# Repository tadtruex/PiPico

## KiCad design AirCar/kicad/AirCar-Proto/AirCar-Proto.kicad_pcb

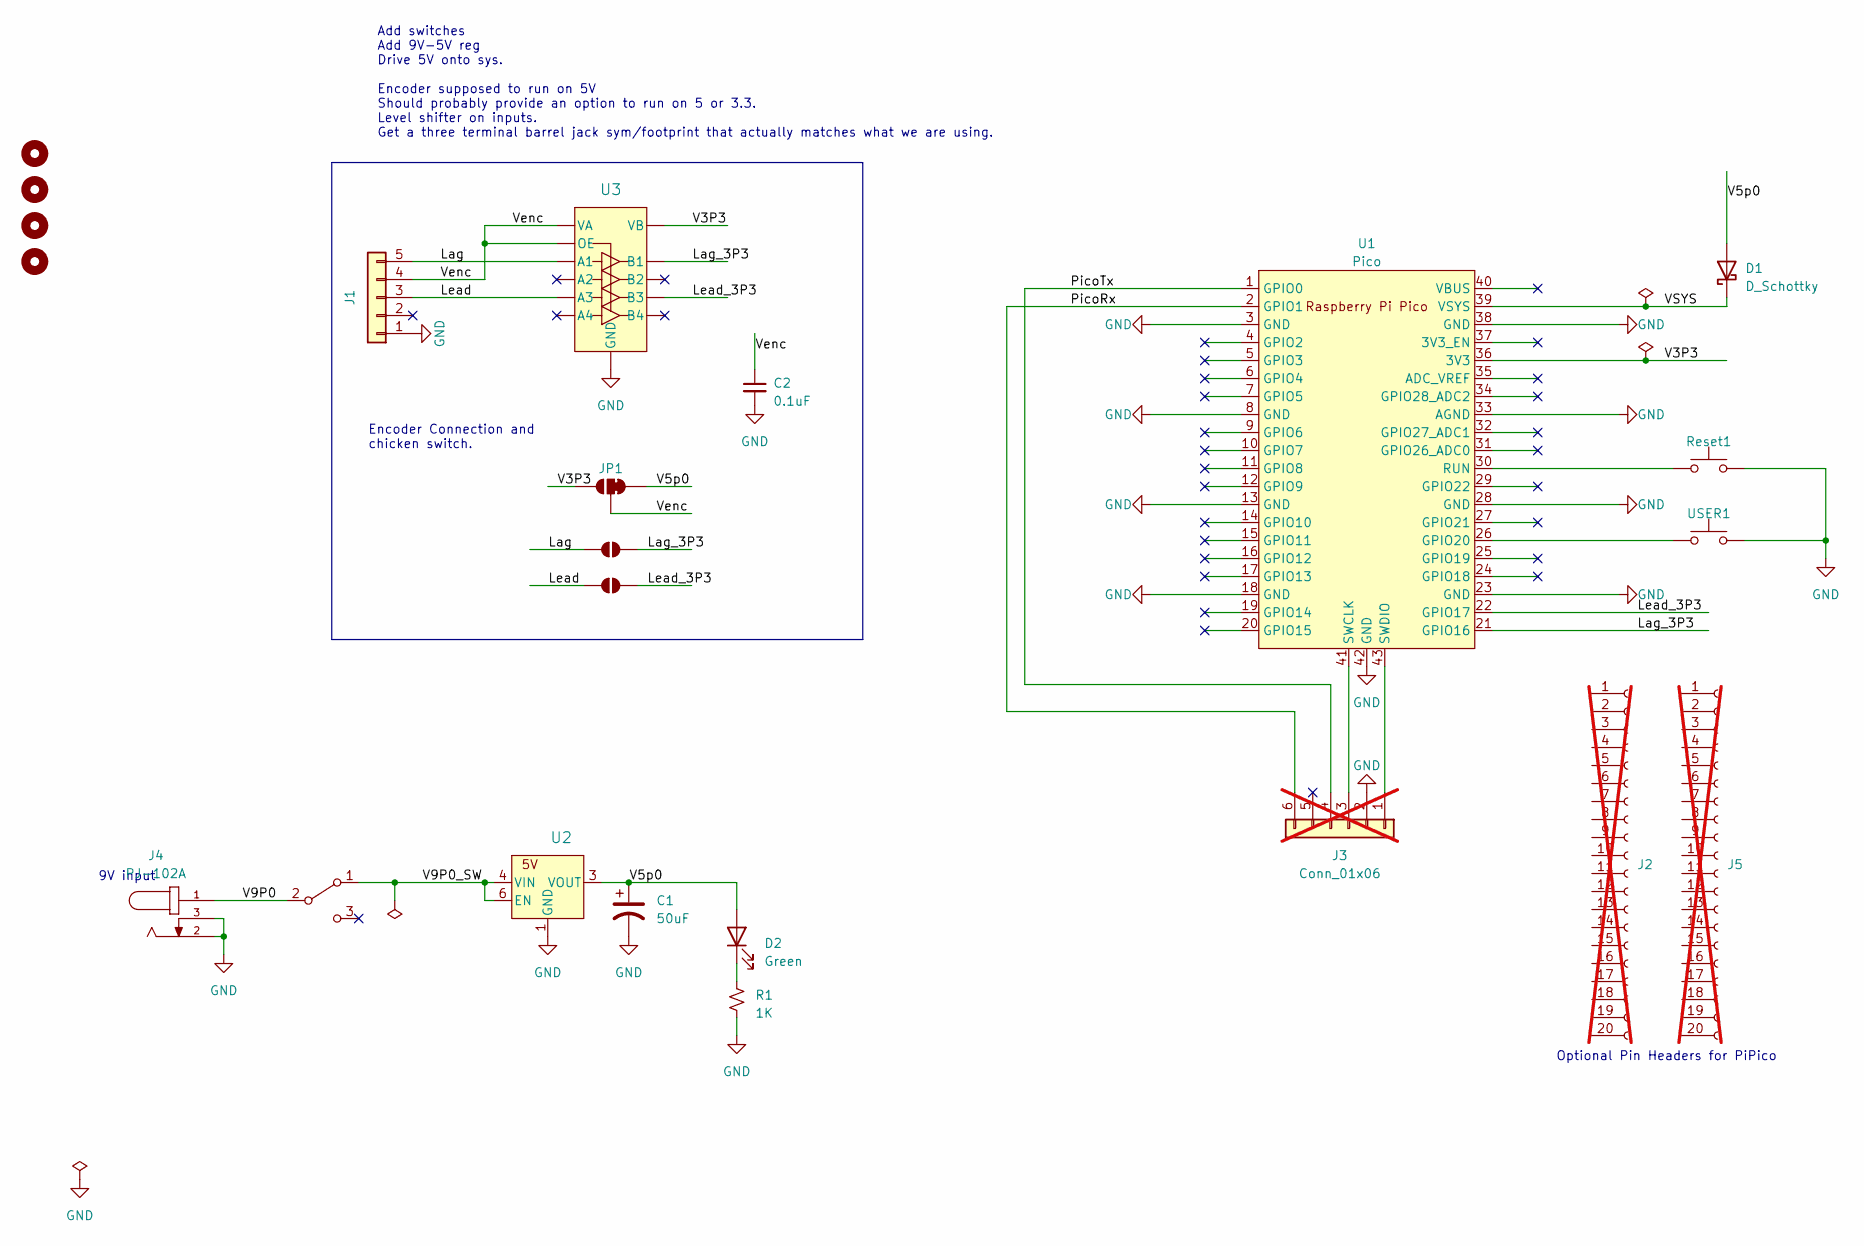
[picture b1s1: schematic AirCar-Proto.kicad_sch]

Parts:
C1: 50uF; CP_Radial_D8.0mm_P2.50mm
C2: 0.1uF; C_0603_1608Metric
D1: D_Schottky; D_SOD-123F; Digikey CRS01QCT-ND
D2: Green; LED_D5.0mm
H1, H2, H3, H4: MountingHole; MountingHole_3.2mm_M3
J1: Conn_01x05; PinHeader_1x05_P2.54mm_Horizontal; Digikey WM4903-ND
J2, J5: Conn_01x20_Socket; PinHeader_1x20_P2.54mm_Vertical; DigiKey 1212-1105-ND; not fitted
J3: Conn_01x06; PinHeader_1x06_P2.54mm_Horizontal; not fitted
J4: PJ-102A; BarrelJack_CUI_PJ-102AH_Horizontal; PART_REV 1.03
JP1: SolderJumper_3_Bridged12; SolderJumper-3_P1.3mm_Bridged12_RoundedPad1.0x1.5mm
JP2, JP3: SolderJumper_2_Open; SolderJumper-2_P1.3mm_Open_RoundedPad1.0x1.5mm
R1: 1K; R_0603_1608Metric
Reset1: SmallPushbutton; SW4_1825910-B_TEC; Digikey 450-1650-ND
SW2: SW_SPDT; CS12ANW03_NKK; Digikey 360-2131-ND
U1: Pico; RPi_Pico_SMD_TH; Digikey 2648-SC0915TR-ND
U2: LDL212PU50R; DFN-6-1EP_3x3mm_P0.95mm_EP1.7x2.6mm; Digikey 497-16897-2-ND
U3: TXU0104BQAR; U_TXU0104_TEX; Digikey 296-TXU0104BQARTR-ND
USER1: SmallPushbutton; SW4_1825910-B_TEC; Digikey 450-1650-ND

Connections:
/Lag: J1.5, JP2.1 (A), U3.2 (A1)
/Lag_3P3: JP2.2 (B), U1.21 (GPIO16), U3.13 (B1)
/Lead: J1.3, JP3.1 (A), U3.4 (A3)
/Lead_3P3: JP3.2 (B), U1.22 (GPIO17), U3.11 (B3)
/PicoRx: J3.6, U1.2 (GPIO1)
/PicoTx: J3.4, U1.1 (GPIO0)
/V3P3: JP1.3 (B), U1.36 (3V3), U3.14 (VB)
/V5p0: C1.1, D1.2 (A), D2.2 (A), JP1.1 (A), U2.2 (ADJ/sense), U2.3 (VOUT)
/V9P0: J4.1, SW2.2 (B)
/V9P0_SW: SW2.1 (A), U2.4 (VIN), U2.6 (EN)
/VSYS: D1.1 (K), U1.39 (VSYS)
/Venc: C2.1, J1.4, JP1.2 (C), U3.1 (VA), U3.8 (OE)
GND: C1.2, C2.2, J1.1, J3.2, J4.2, J4.3, R1.2, Reset1.3, Reset1.4, U1.3 (GND), U1.8 (GND), U1.13 (GND), U1.18 (GND), U1.23 (GND), U1.28 (GND), U1.33 (AGND), U1.38 (GND), U1.42 (GND), U2.1 (GND), U2.7 (GND), U3.7 (GND), U3.15 (GND), USER1.3, USER1.4
unnamed: D2.1 (K), R1.1
unnamed: J3.1, U1.43 (SWDIO)
unnamed: J3.3, U1.41 (SWCLK)
unnamed: U1.26 (GPIO20), USER1.1, USER1.2
unnamed: Reset1.1, Reset1.2, U1.30 (RUN)

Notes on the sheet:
Add switches Add 9V-5V reg Drive 5V onto sys. Encoder supposed to run on 5V Should probably provide an option to run on 5 or 3.3. Level shifter on inputs. Get a three terminal barrel jack sym/footprint that actually matches what we are using.
Optional Pin Headers for PiPico
9V input
Encoder Connection and chicken switch.

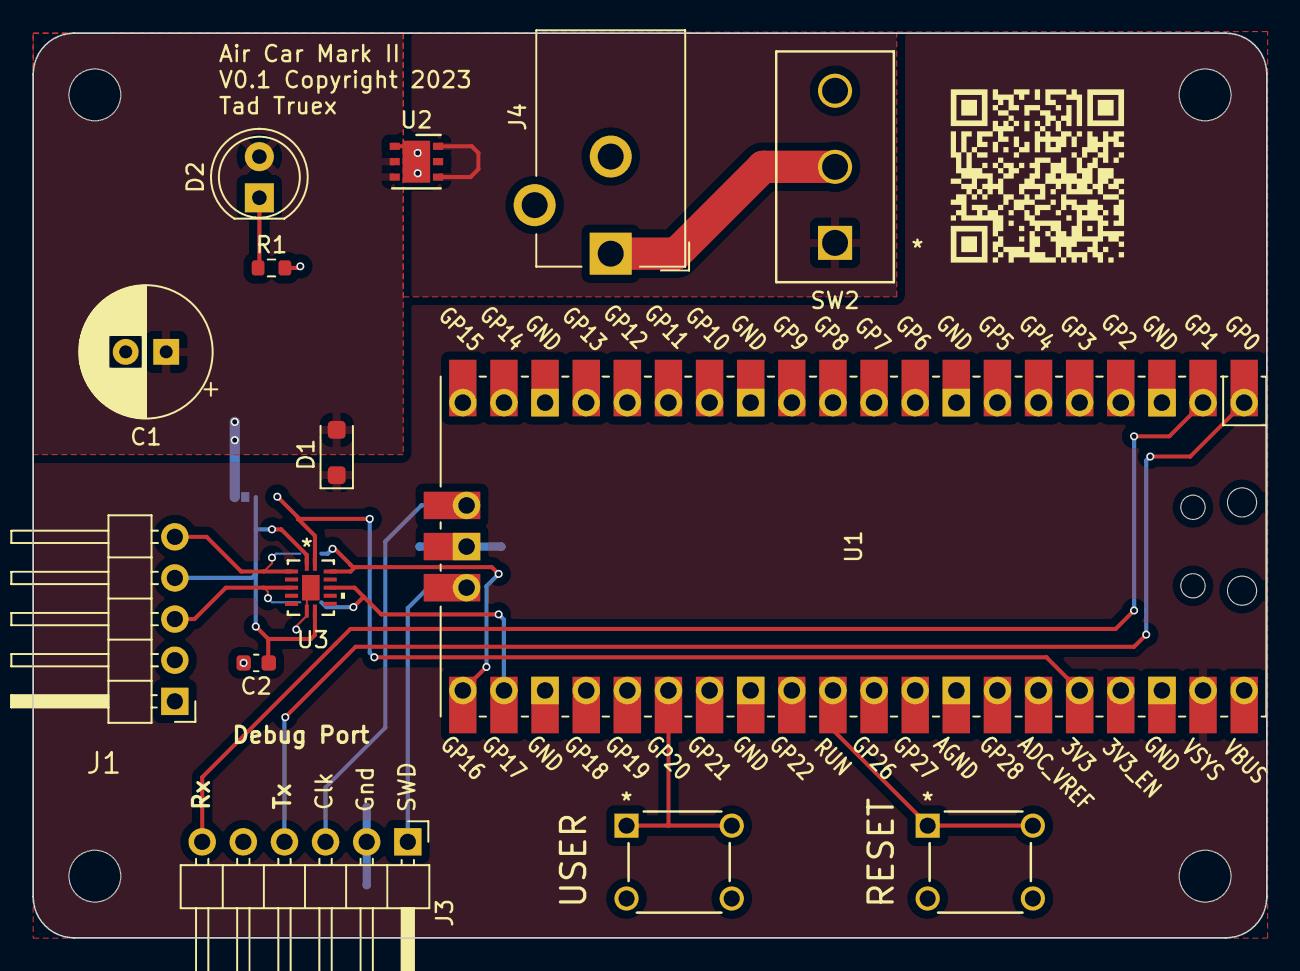
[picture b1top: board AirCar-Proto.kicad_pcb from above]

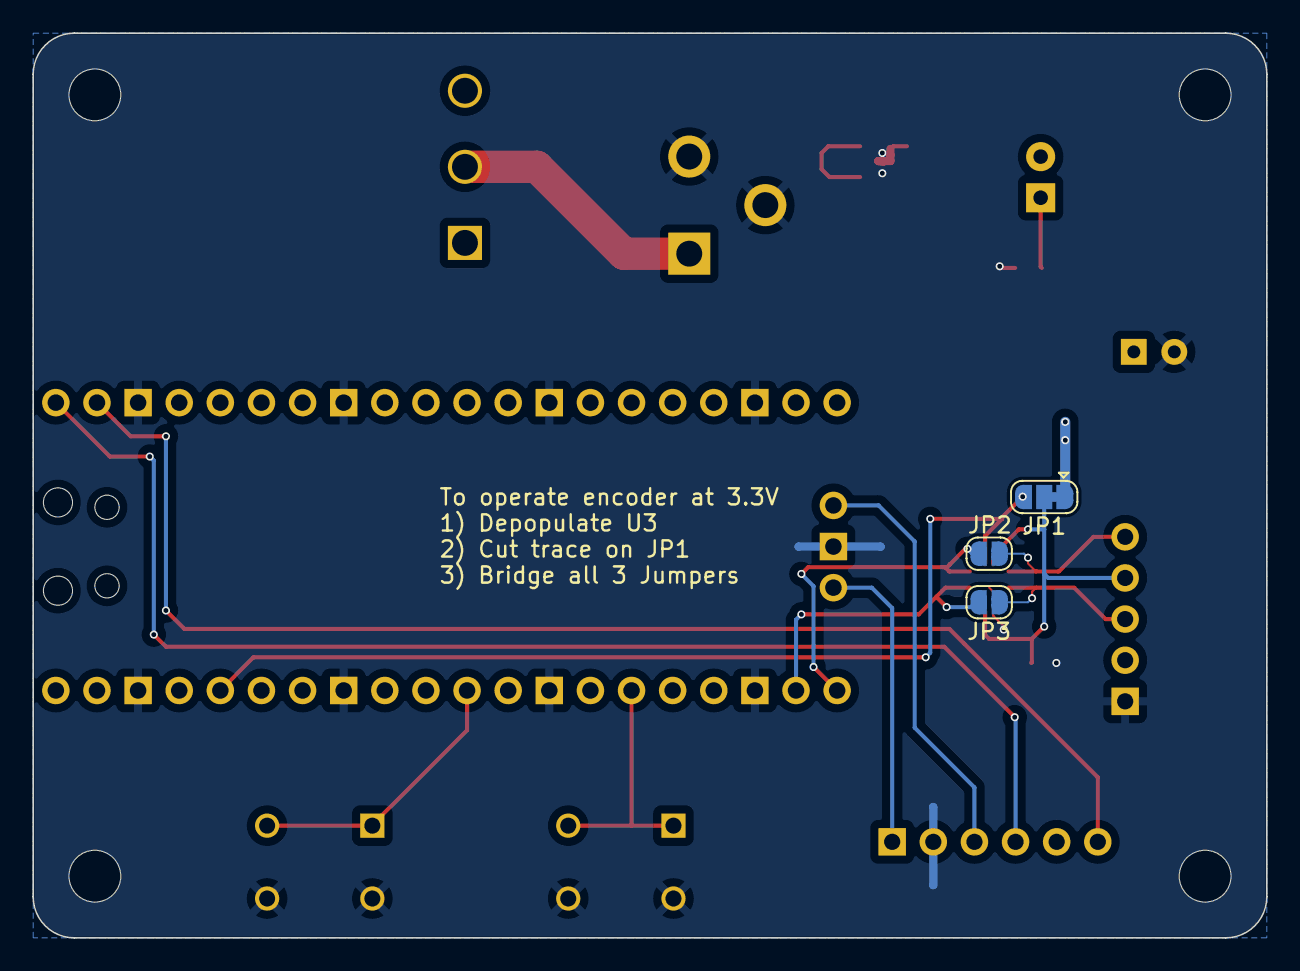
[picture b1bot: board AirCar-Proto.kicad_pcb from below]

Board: 2 copper layers, 76.2 x 55.9 mm, 21 parts (3 on the bottom side), 18 nets.

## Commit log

2023-09-18 add examples back in
2023-09-20 Add empty placeholder for air car firmware.
2023-09-20 Start playing with interrupt handler
2023-09-21 add pdf docs
2023-09-21 work on encoder
2023-09-21 add some caveman debugging
2023-09-22 start adding timer
2023-09-22 Start working on timer functionality.
    Start to address #8
2023-09-22 add heartbeat and work around bug - sample rate is 28us
2023-09-25 Add pwm lib to CMake
    Use PWM to generate 28.2us square-ish wave on pin 4.
    Partially addresses #8
2023-09-25 Add the msc_dual_lun example as a standalone secondary target.
    Mostly as an excercise in figuring out how CMake works...
2023-09-26 Finally find the magic required to get something with both pico-sdk and tinyusb to compile.
2023-09-26 aircar now appears as a usb device (actually 2). Cribbed most of the code from the tinyusb libraries example code.
    There are currently no callbacks implemented and no real filesystem.
    Closes #3
2023-09-26 This add the fatfs everyone seems to use. Ultimately can probably move it out of the local area as it is included in tinyusb.
    Start fleshing out a ram disk driver.
    Close #11
    Work on #12
2023-09-27 Flesh out the ramdisk driver. Passes the fatfs driver test (which isn't too demanding)
2023-09-27 may have a file in the new ramdisk now
2023-09-28 Very (very) lightly tested read of fatfs on ramdisk over USB.
2023-09-28 read and write seem to work from USBland
2023-09-28 add rudimentary versioning
2023-09-28 start adding interrupt
2023-09-29 Make the PWM interrupt highest priority and enable it.
    Timebase is not very accurate when compiled for debug, so don't do that
    anymore...
    cmake --build -DCMAKE_BUILD_TYPE=Release
2023-09-29 This is broken. There seems to be some sort of interaction between the PWM interrupt and the rest of the system, particulary UART stdio...
2023-10-02 fix the pwm interrupt. Now need to process data before fwriting it
2023-10-02 work on new file
2023-10-02 Quirky but worky.
    Basically works OK. A few issues.
    1) It doesn't appear possible (or easy at least) to cause the host computer
    to re-read the disk after it is inserted. This makes development a bit of a pain...
    Probably possibly to have it disconnect in software, but not sure.
    Anyway - this firmware seems to track that on Car F very closely. Need some testing
    and breaking, but should be close.
2023-10-03 add start of schematic
2023-10-04 Add rudimentary schematic for proto-board version.
    Note: This schematic runs the rotary encoder below it's minimum
    VDD value. It seems to work fine (as it should), but it may be
    flaky.
    This fixes a bug in the stateUpdate logic that manifests when the
    lead pin is higher (pin number) than the lag pin.
2023-10-04 turn led off when collecting data
2023-10-05 Add durable storage
    Close #14
2023-10-05 bump version
2023-12-01 start working on board
2023-12-11 work on proto
2023-12-11 Good start.
    Need to add 3v/5v option for encoder.
2023-12-12 works w/ 3.3v encoder
2023-12-13 work on adding level shifter
2023-12-15 switch to some none through hole parts because SMD is easier...
2023-12-15 possible rev 0.1 candidate
2023-12-15 Gerbers for initial proto
2023-12-18 remove small vias for JLCPCB
2023-12-27 add pin headers and BOM
2024-01-04 Reduce data to 720 samples ( -10% )
    Reduce start delay to 45 degrees.

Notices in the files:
AirCar/kicad/AirCar-Proto/AirCar-Proto.kicad_pcb:
V0.1 Copyright 2023
